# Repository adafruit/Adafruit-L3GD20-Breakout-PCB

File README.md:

## Adafruit L3GD20H Triple-Axis Gyro Breakout Board PCB
<a href="http://www.adafruit.com/products/1032"><br/>
Click here to purchase one from the Adafruit shop</a>

A gyroscope is a type of sensor that can sense twisting and turning motions. Often paired with an accelerometer, you can use these to do 3D motion capture and inertial measurement (that is - you can tell how an object is moving!) As these sensors become more popular and easier to manufacture, the prices for them have dropped to the point where you can easily afford a triple-axis gyro! Only a decade ago, this space-tech sensor would have been hundreds of dollars.

This breakout board is based around the latest gyro technology, the L3GD20H from STMicro. It's the upgrade to the L3G4200 (see this app note on what to look for if upgrading an existing design to the L3GD20) with three full axes of sensing. The chip can be set to ±250, ±500, or ±2000 degree-per-second scale for a large range of sensitivity. There's also built in high and low pass sensing to make data processing easier. The chip supports both I2C and SPI so you can interface with any microcontroller easily.

PCB files for the Adafruit L3GD20 Breakout. The format is EagleCAD schematic and board layout
- https://www.adafruit.com/product/1032

### License

Adafruit invests time and resources providing this open source design, please support Adafruit and open-source hardware by purchasing products from [Adafruit](https://www.adafruit.com)!

All text above must be included in any redistribution

Designed by Limor Fried/Ladyada for Adafruit Industries.
Creative Commons Attribution/Share-Alike, all text above must be included in any redistribution. 
See license.txt for additional information.

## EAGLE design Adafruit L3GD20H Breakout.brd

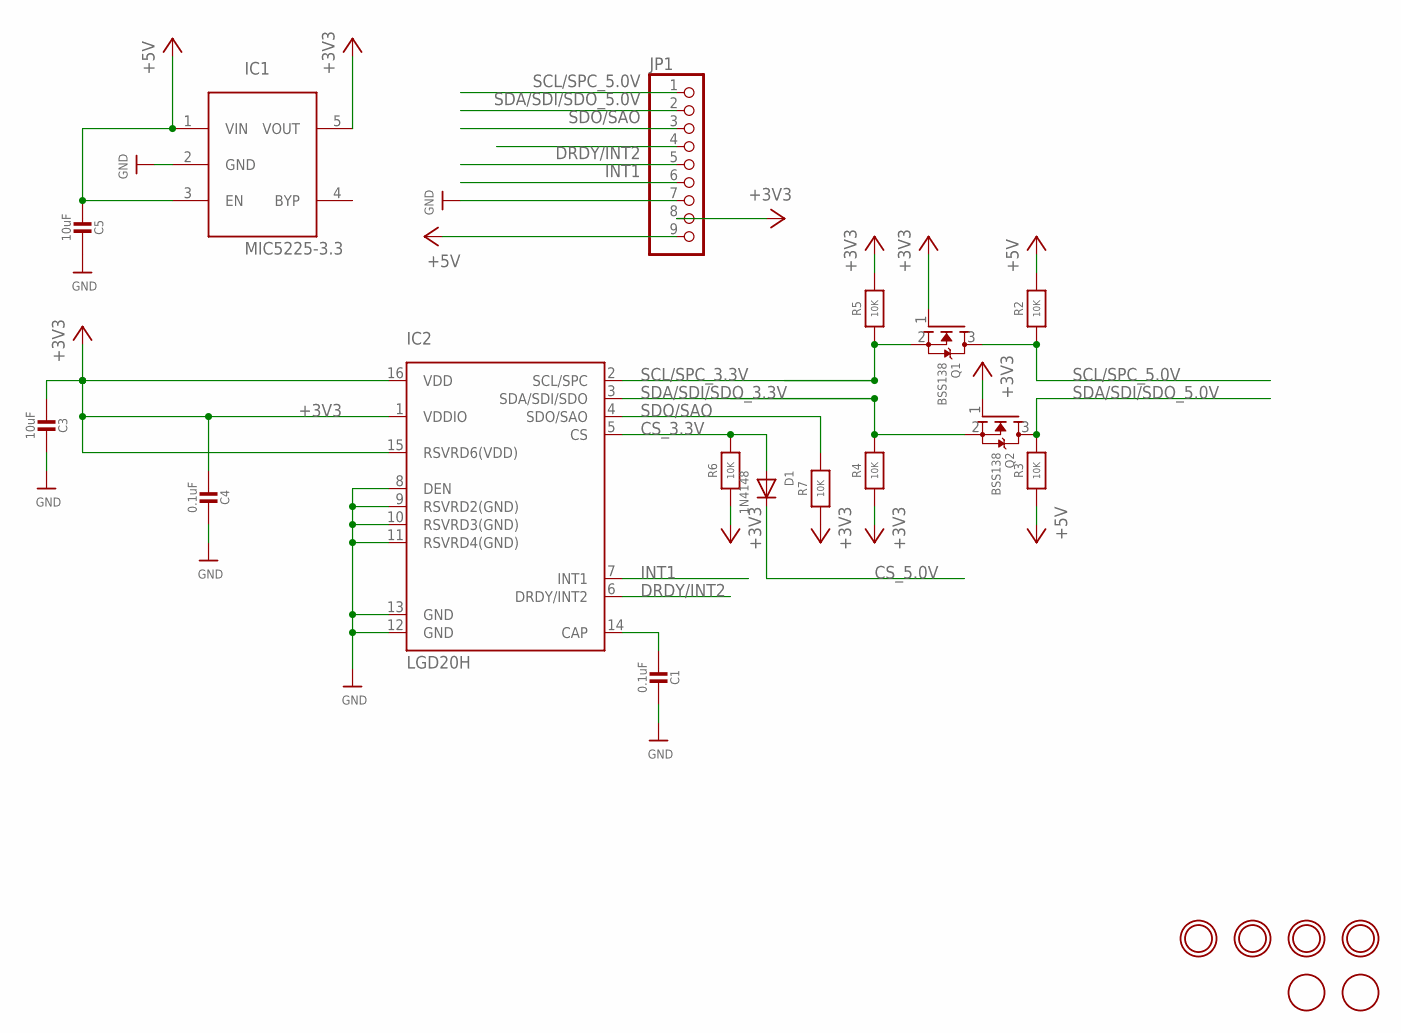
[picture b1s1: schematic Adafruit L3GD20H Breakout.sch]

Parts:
C1, C4: 0.1uF; 0805-NO
C3, C5: 10uF; 0805-NO
D1: 1N4148; SOD-323F
IC1: MIC5225-3.3; SOT23-5L
IC2: LGD20H; L3GD20H_LGA16L
JP1: HEADER-1X976MIL; 1X09_ROUND_76
Q1, Q2: BSS138; SOT23
R2, R4, R5, R7: 10K; 0805-NO
R3, R6: 10K; _0805MP
U$11, U$12, U$13, U$14: MOUNTINGHOLE2.0; MOUNTINGHOLE_2.0_PLATED
U$15, U$16: FIDUCIAL; FIDUCIAL_1MM

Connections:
+3V3: C3.2, C4.2, IC1.5 (VOUT), IC2.1 (VDDIO), IC2.15 (RSVRD6(VDD)), IC2.16 (VDD), JP1.8, Q1.1 (G), Q2.1 (G), R4.1, R5.2, R6.1, R7.1
+5V: C5.2, IC1.1 (VIN), IC1.3 (EN), JP1.9, R2.2, R3.1
CS_3.3V: D1.A, IC2.5 (CS), R6.2
CS_5.0V: D1.C, JP1.4
DRDY/INT2: IC2.6 (DRDY/INT2), JP1.5
GND: C1.1, C3.1, C4.1, C5.1, IC1.2 (GND), IC2.8 (DEN), IC2.9 (RSVRD2(GND)), IC2.10 (RSVRD3(GND)), IC2.11 (RSVRD4(GND)), IC2.12 (GND), IC2.13 (GND), JP1.7
INT1: IC2.7 (INT1), JP1.6
unnamed: C1.2, IC2.14 (CAP)
SCL/SPC_3.3V: IC2.2 (SCL/SPC), Q1.2 (S), R5.1
SCL/SPC_5.0V: JP1.1, Q1.3 (D), R2.1
SDA/SDI/SDO_3.3V: IC2.3 (SDA/SDI/SDO), Q2.2 (S), R4.2
SDA/SDI/SDO_5.0V: JP1.2, Q2.3 (D), R3.2
SDO/SAO: IC2.4 (SDO/SAO), JP1.3, R7.2

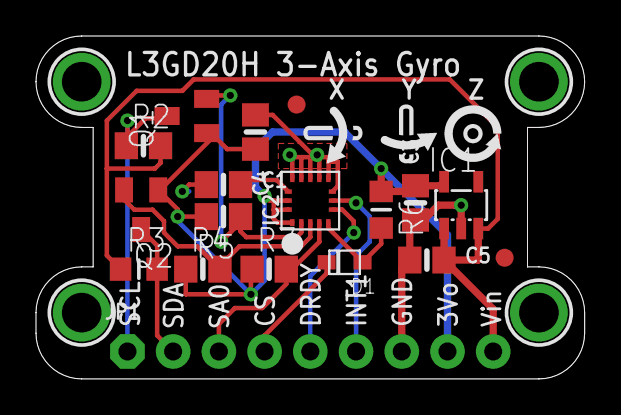
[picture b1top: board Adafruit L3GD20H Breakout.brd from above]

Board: 2 copper layers, 30.5 x 19.1 mm, 24 parts (1 on the bottom side), 13 nets.

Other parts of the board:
U$3: SYMBOL_GYROXYZ_10MM
U$10: ADAFRUIT_TEXT_20MM

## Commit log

2016-06-06 init
